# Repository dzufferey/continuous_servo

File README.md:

# Continous Servo

## BoM

* [Teensy LC](https://www.pjrc.com/teensy/teensyLC.html)
* Electric motor with quadrature encoder ([pololu metal gearbox motor 25D with 48 CPR encoder](https://www.pololu.com/product/3239)) with mounting bracket ([Pololu 25D mm Metal Gearmotor Bracket Pair](https://www.pololu.com/product/2676))
* [MAX14870 Single Brushed DC Motor Driver Carrier](https://www.pololu.com/product/2961)
* Voltage regulator that output 5V ([Pololu Adjustable Step-Up/Step-Down Voltage Regulator S7V8A](https://www.pololu.com/product/2118))
* Through-hole resistors: 2 x 39kΩ, 2 x 68kΩ
* Electrolitic capacitors: ...
* 12V PSU with 5mm/2.1mm barrel jack
* female adapter for 5mm/2.1mm barrel jack
* headers and stuffs ...

## Attributions

* The Kicad modules for Teensy-LC was adapted from the code at https://github.com/hedrickbt/teensy_breakout by Brooke Hedrick released under MIT License.
* `resources/max14870.wrl` is derived from [MAX14870 Single Brushed DC Motor Driver Carrier model by Pololu](https://www.pololu.com/file/0J1338/max14870-single-brushed-dc-motor-driver-carrier.step), license unclear ...

## License

The content of this project itself (excluding attributed parts) is licensed under the Creative Commons Attribution 3.0 license, and the source code in the `motor_pid` folder is licensed under the MIT license.

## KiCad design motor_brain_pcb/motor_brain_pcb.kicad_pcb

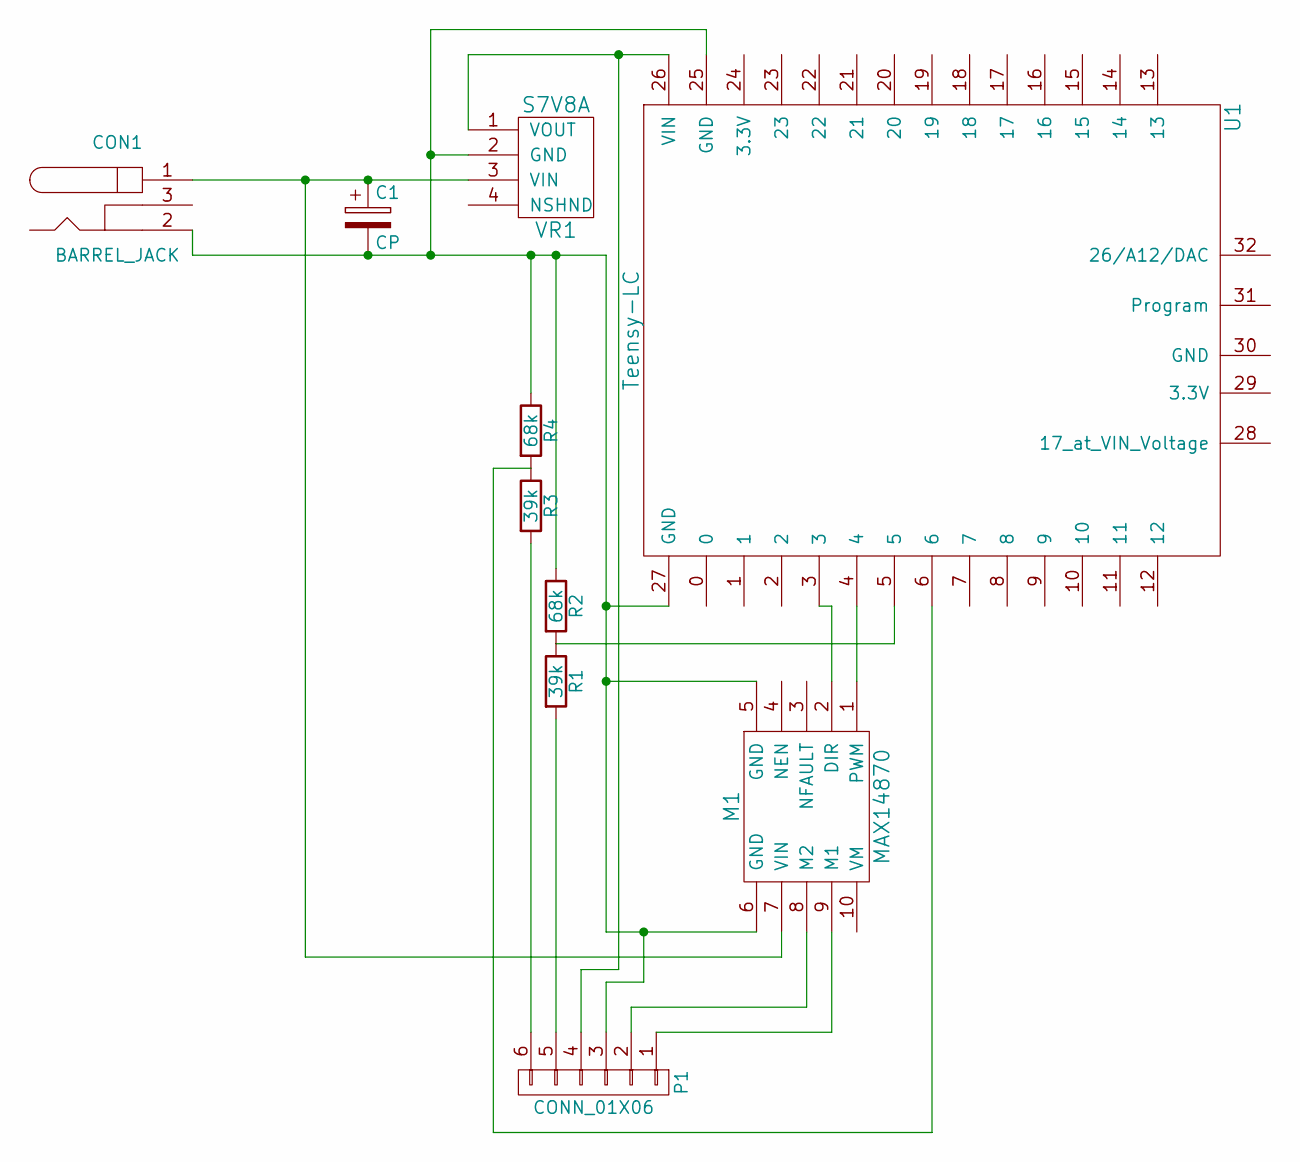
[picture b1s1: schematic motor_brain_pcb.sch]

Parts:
C1: CP; C_Radial_D10_L16_P5
CON1: BARREL_JACK
M1: MAX14870
P1: CONN_01X06; Socket_Strip_Straight_1x06
R1, R3: 39k; Resistor_Horizontal_RM10mm
R2, R4: 68k; Resistor_Horizontal_RM10mm
U1: Teensy-LC; teensy-lc
VR1: S7V8A

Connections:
unnamed: C1.1, CON1.1, M1.7 (VIN), VR1.3 (VIN)
unnamed: C1.2, CON1.2, M1.5 (GND), M1.6 (GND), P1.3, R2.1, R4.1, U1.25 (GND), U1.27 (GND), VR1.2 (GND)
unnamed: M1.1 (PWM), U1.4
unnamed: M1.2 (DIR), U1.3
unnamed: M1.8 (M2), P1.2
unnamed: M1.9 (M1), P1.1
unnamed: P1.4, U1.26 (VIN), VR1.1 (VOUT)
unnamed: P1.5, R1.2
unnamed: P1.6, R3.2
unnamed: R1.1, R2.2, U1.5
unnamed: R3.1, R4.2, U1.6

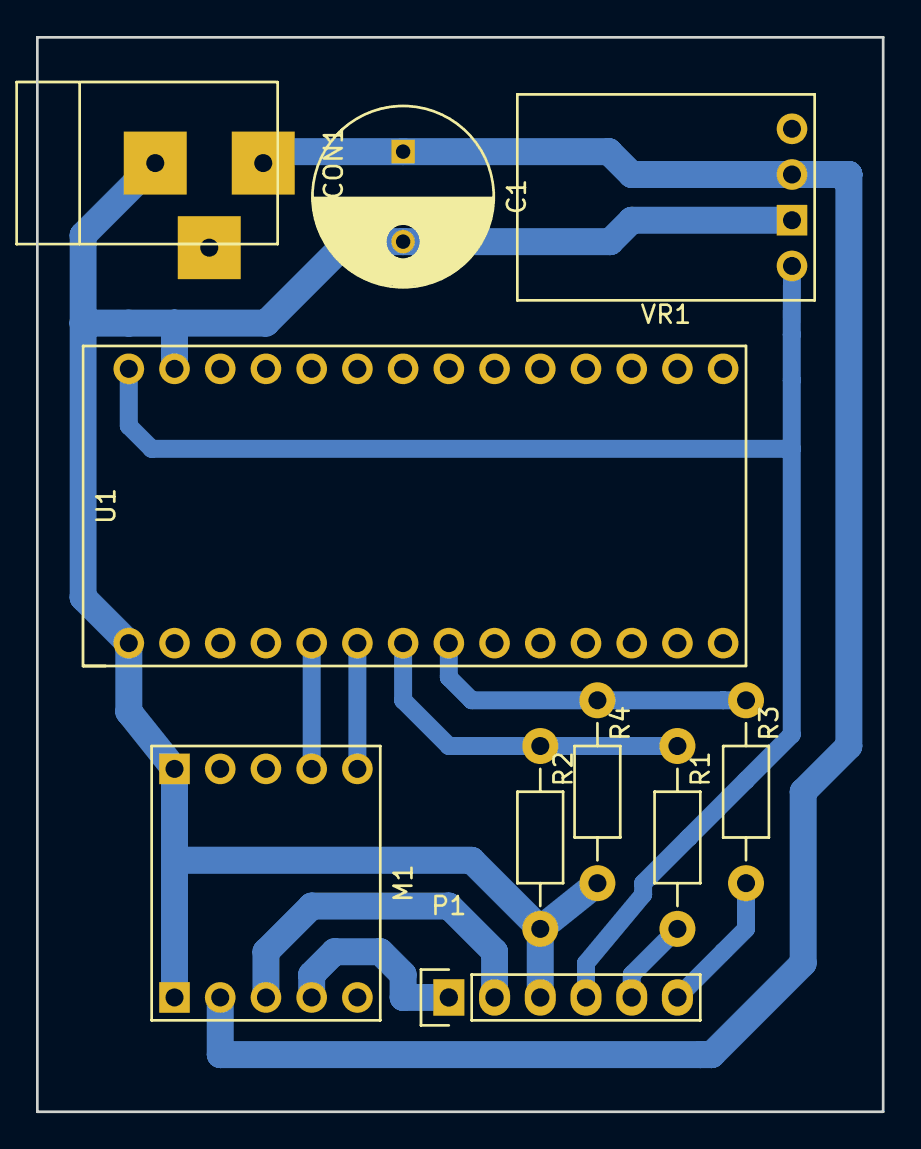
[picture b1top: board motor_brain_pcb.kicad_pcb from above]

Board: 2 copper layers, 47.0 x 59.7 mm, 10 parts (0 on the bottom side), 11 nets.

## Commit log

2017-09-04 1st draft
2017-09-04 updating attributions
2017-09-07 code: control speed or position
2017-09-12 wired the encoder backward
2017-09-12 tuning PID
2017-09-17 adding some models and info
2017-09-19 output files to new folder
